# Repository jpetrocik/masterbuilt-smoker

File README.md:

# Smart Smoker Controller System

This project replaces the standard control board in an electric smoker, adding Wi-Fi, PID heat control, four built-in meat probes, a companion mobile app, and more. I can remotely monitor and control the cook from anywhere without being tied down to the smoker. The custom PID algorithm maintains an almost perfect internal temperature with minimal fluctuations. A variety of push notifications eliminate the need to constantly check on the cook throughout the day and night.

The primary goal of this project is to give me my weekend back. I don't want to constantly babysit the smoker when I rather be spending the day snowboarding, hitting trails, off-roading, or just hanging out with friends. The controller continuously monitors the smoker and meat temperature, sending real-time notifications to my phone when probes hit their target temperatures.

This specific board was designed as a drop-in replacement for Masterbuilt refrigerator-style smokers, but the system can be adapted to work with almost any electric smoker.

## Overview

This repository is split into four major components, each with its own detailed `README.md` file:

### 1. Mobile App (./www/README.md)
A Progressive Web App (PWA) that can be installed on your phone to run exactly like a native app, complete with real-time push notifications.

### 2. Backend (./server/README.md)
The central nervous system of the project. It acts as the bridge between the physical smoker and the mobile application. The backend handles the complex algorithms for stall detection and logs high-resolution temperature history. The system is highly fault-tolerant: if the backend drops offline, the firmware will continue executing the active cook locally. If the backend loses connection to the smoker, an alert is sent immediately to your phone.

### 3. Firmware (./firmware/README.md)
The embedded code running on the physical microcontroller (ESP32) that directly interfaces with the smoker's hardware.

### 4. Hardware & PCBs (./hardware/README.md)
This directory contains the custom board designs. Currently, there are two boards designed to support Masterbuilt smokers: the main controller PCB and the power module. The custom power module replaces the stock mechanical relay with a Solid State Relay (SSR) to easily tolerate the rapid on/off switching required by the PID heat control.

## 📂 Repository Structure

```text
├── /server             # Node.js backend
├── /firmware           # Microcontroller code (ESP32/Arduino)
├── /www                # React / Vite / Tailwind PWA
├── /hardware           # Schematics and Gerber files
└── README.md           # Project overview (You are here)

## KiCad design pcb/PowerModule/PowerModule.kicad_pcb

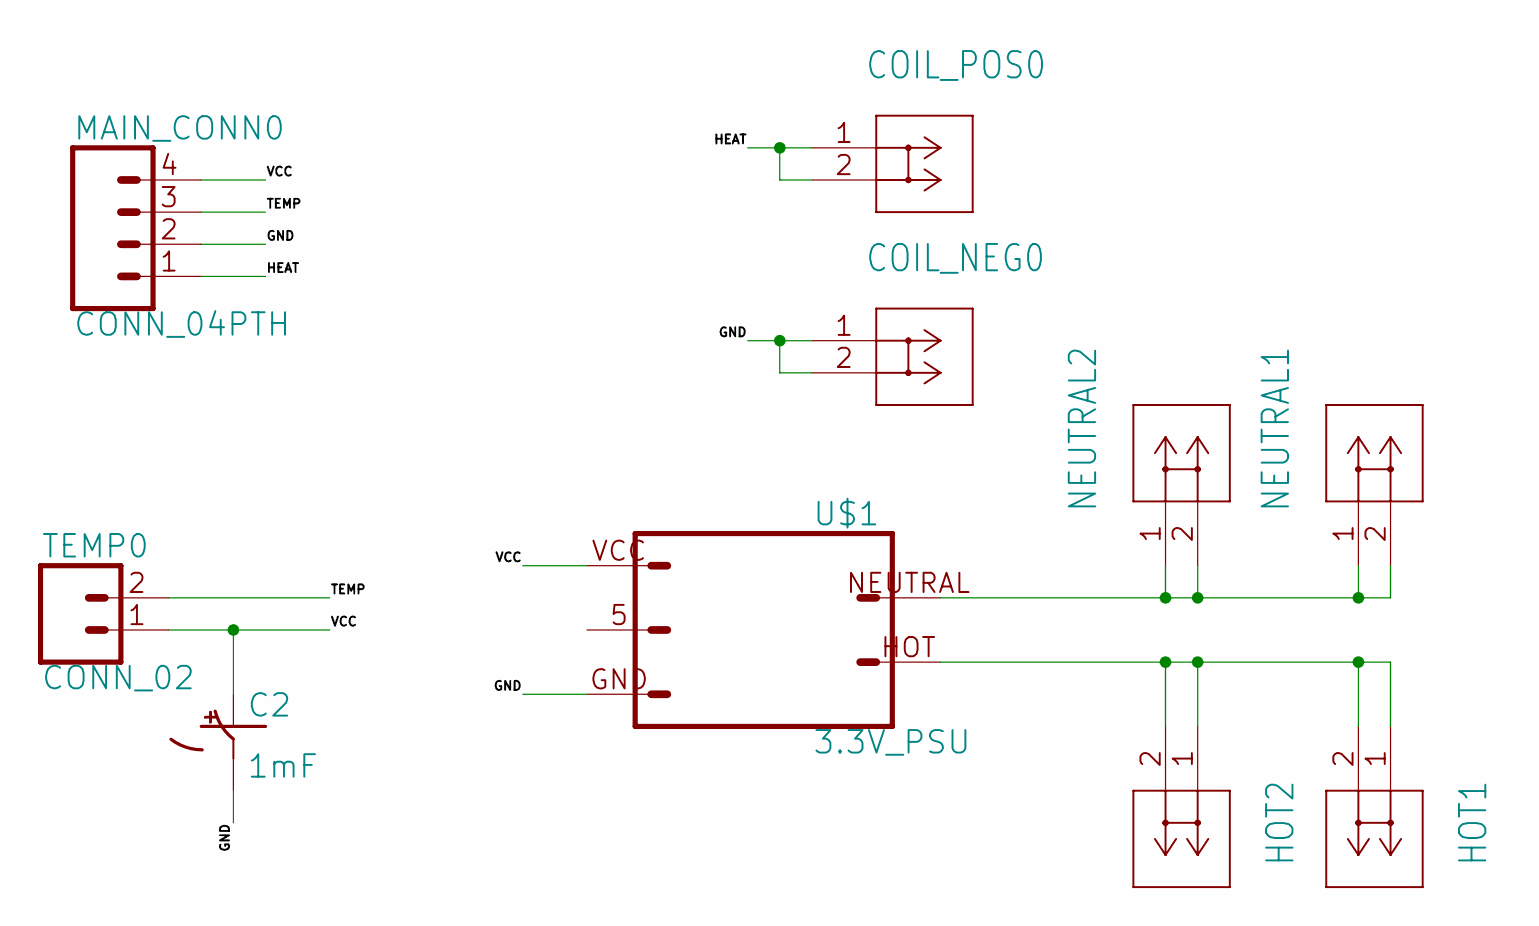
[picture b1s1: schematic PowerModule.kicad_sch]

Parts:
C2: 1mF; CPOL-RADIAL-5MM-10MM
COIL_NEG0: 1287; CONN_1287_KEY
COIL_POS0: 1287; CONN_1287_KEY
HOT1, HOT2: 1287; CONN_1287_KEY
MAIN_CONN0: CONN_04PTH; 1X04
NEUTRAL1, NEUTRAL2: 1287; CONN_1287_KEY
TEMP0: CONN_02; 1X02
U$1: 3.3V_PSU; 1X03

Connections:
GND: C2.-, COIL_NEG0.1, COIL_NEG0.2, MAIN_CONN0.2, U$1.GND
HEAT: COIL_POS0.1, COIL_POS0.2, MAIN_CONN0.1
HOT: HOT1.1, HOT1.2, HOT2.1, HOT2.2, U$1.HOT
NEUTRAL: NEUTRAL1.1, NEUTRAL1.2, NEUTRAL2.1, NEUTRAL2.2, U$1.NEUTRAL
TEMP: MAIN_CONN0.3, TEMP0.2
VCC: C2.+, MAIN_CONN0.4, TEMP0.1, U$1.VCC

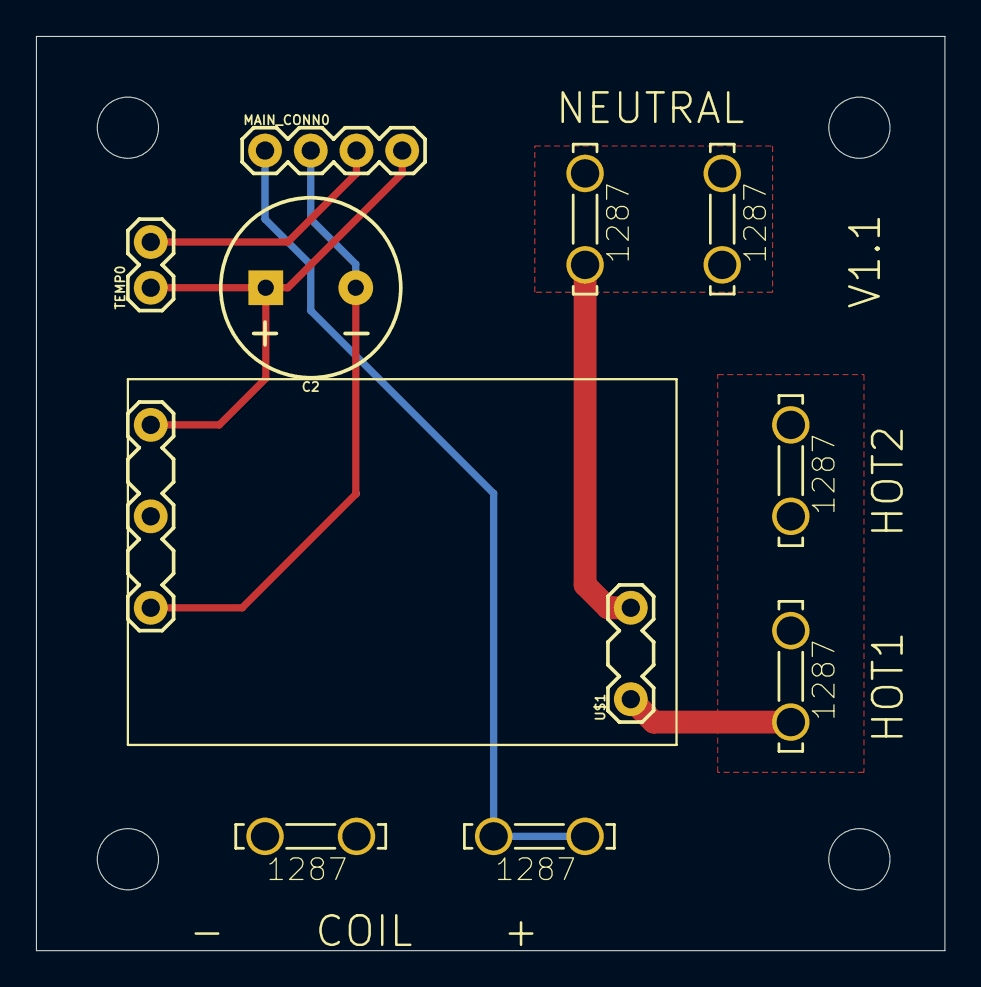
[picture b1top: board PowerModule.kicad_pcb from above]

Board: 2 copper layers, 50.5 x 50.8 mm, 14 parts (0 on the bottom side), 6 nets.

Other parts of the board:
UNK_HOLE_0: dummyfp0
UNK_HOLE_1: dummyfp1
UNK_HOLE_2: dummyfp2
UNK_HOLE_3: dummyfp3

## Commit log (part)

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2022-12-12 Inital commit
2022-12-12 WebSocket
2022-12-12 probes
2022-12-13 No working PID
2022-12-14 Working PID
2022-12-17 Added cookEndTime
2023-01-18 Added probe
2023-02-26 New PROBE_A/B/C
2023-02-27 Added OTA
2023-02-27 Tweaker kp,ki,kd
2023-03-09 Tweaking temp coiffients
2023-03-09 Added eagle files
2023-03-09 Create README.md
    Added readme.md
2023-03-12 using adc functions and new thermistor a/b/c
2023-08-22 Initial commit after some calibration
2023-08-24 Port of PIP
2025-03-12 Add kicad files
2025-05-29 kicad files
2025-05-29 compiles
2025-06-02 Switching to ADS1115
2025-06-03 Probes working with ADS1115
2025-08-02 board version 2.0
2025-08-02 Renamed files
2025-08-12 Removed escape character
2025-08-12 Added developement notes
2025-08-12 Added deep orange theme samples
2025-08-13 Removed bad files
2025-08-13 Added LCD support
2025-08-13 Added define to enable/disable LCD
2025-08-13 upstream lv.conf
2025-08-13 Configure lv.conf file
2025-08-15 Added initial mqqtt support (WIP)
2025-08-15 Configure TFT User_Setup.h
2025-08-15 Moved websoceket and wfi code into sperate files
2025-08-15 Cleaned up UI and better wifi init
2025-08-15 mqtt publish status working
2025-08-15 Changed CommandEvent handling to parse in main.cpp
2025-08-25 Fixed devide by zero error
2025-08-25 Fix overflow issue
2025-08-25 Updated probe ABC numbers
2025-08-26 Temp ABC
2025-08-26 New ABC
2025-08-26 add set check limits
2025-08-26 Cleaned up logging
2025-08-26 Added last will MQTT message
2025-08-27 Added debugProbe and new ABC values
2025-08-27 Added back dutyCycle
2025-08-27 new temp abc
2025-08-27 Cleanup debug code
2025-09-08 Improved PID and ABC settings
2025-09-08 Minor layout improvements
2025-10-06 v2.1 controller
2025-10-06 Added power modules board
2025-10-07 Adding assests
2025-10-07 update board with lcd
2025-10-11 Fixed issue with UI not compiling
2025-10-13 Removed delay in lcd_loop
2026-01-19 Controller v2.1.1
2026-03-11 Added server backend code
2026-03-11 Added missing spec
2026-03-11 SPEC 0.1 complete
2026-03-11 Initial SPEC 0.2
2026-03-11 initial frontend pass
2026-03-11 Updated state information
2026-03-11 Added Elaspe Time
2026-03-12 Added presence LWT and removed device topic code
2026-03-12 Added simulator
2026-03-12 Renames json properties from probe[X][Property] and prefixed smoker
2026-03-12 Fixed boolean issue with sqllite
2026-03-12 Add similutor launch and .gitignore for sqllite data files
2026-03-12 First pass connected to backend
2026-03-12 Fixed infinite loop and localstorage usage
2026-03-12 Fixed display issue with historical data
2026-03-13 Fixed histroical data
2026-03-14 Firebase
2026-03-18 Firebase notification
2026-03-19 SetTemperature
2026-03-19 SetCookTimer
2026-03-19 sendCommand
2026-03-19 WebSocket nanny
2026-03-19 SmokerId picker
2026-03-19 Deployable build
2026-03-19 Make live data renderig faster
2026-03-19 Presences
2026-03-19 functional complete
2026-03-21 Added simulator command line arguments
2026-03-21 Fixed issue with parsing command line arguments
2026-03-21 Fixed mixed up between probeTemp and probeTarget
2026-03-21 Added manifest
2026-03-23 Create icon assests and icons
2026-03-24 Improved temperature simulation
2026-03-24 Added stale notification and cleaned up notification code
2026-03-24 Improve the telemetry data requirement based on calculated telemetry intervals
2026-03-24 Speed up probe telemetry growth
2026-03-24 Fixed issue with alert on new smoker
2026-03-24 Default notification to true so on startup they are not fired
2026-03-24 Fixed elasped time display to round down
2026-03-24 Fixed issue with timer alter not sending if the timer is reset after the sending and alert the first time
2026-03-25 Fixed issue with history getting deleted on restart
2026-03-25 Rename run script names
2026-03-25 Fixed issue with graph not showing historical data when ws reconnects
2026-03-25 Changed smoker list from last seen to status
2026-03-26 Added time delay notifcation for offline smoker
2026-03-26 Removed offline purge logic
2026-03-26 Reduce historical data to 1 record per minute
2026-03-26 Fix historical record count log message
2026-03-26 Added clickable carousel dot for desktop useablity
2026-03-31 Gated temp between 0 and 300
2026-03-31 Reload smokers when manually launching smoker picker
2026-05-22 Fixed truncated status messages
2026-05-22 Fixed issue with temp increament and decreament button on trigger correctly
